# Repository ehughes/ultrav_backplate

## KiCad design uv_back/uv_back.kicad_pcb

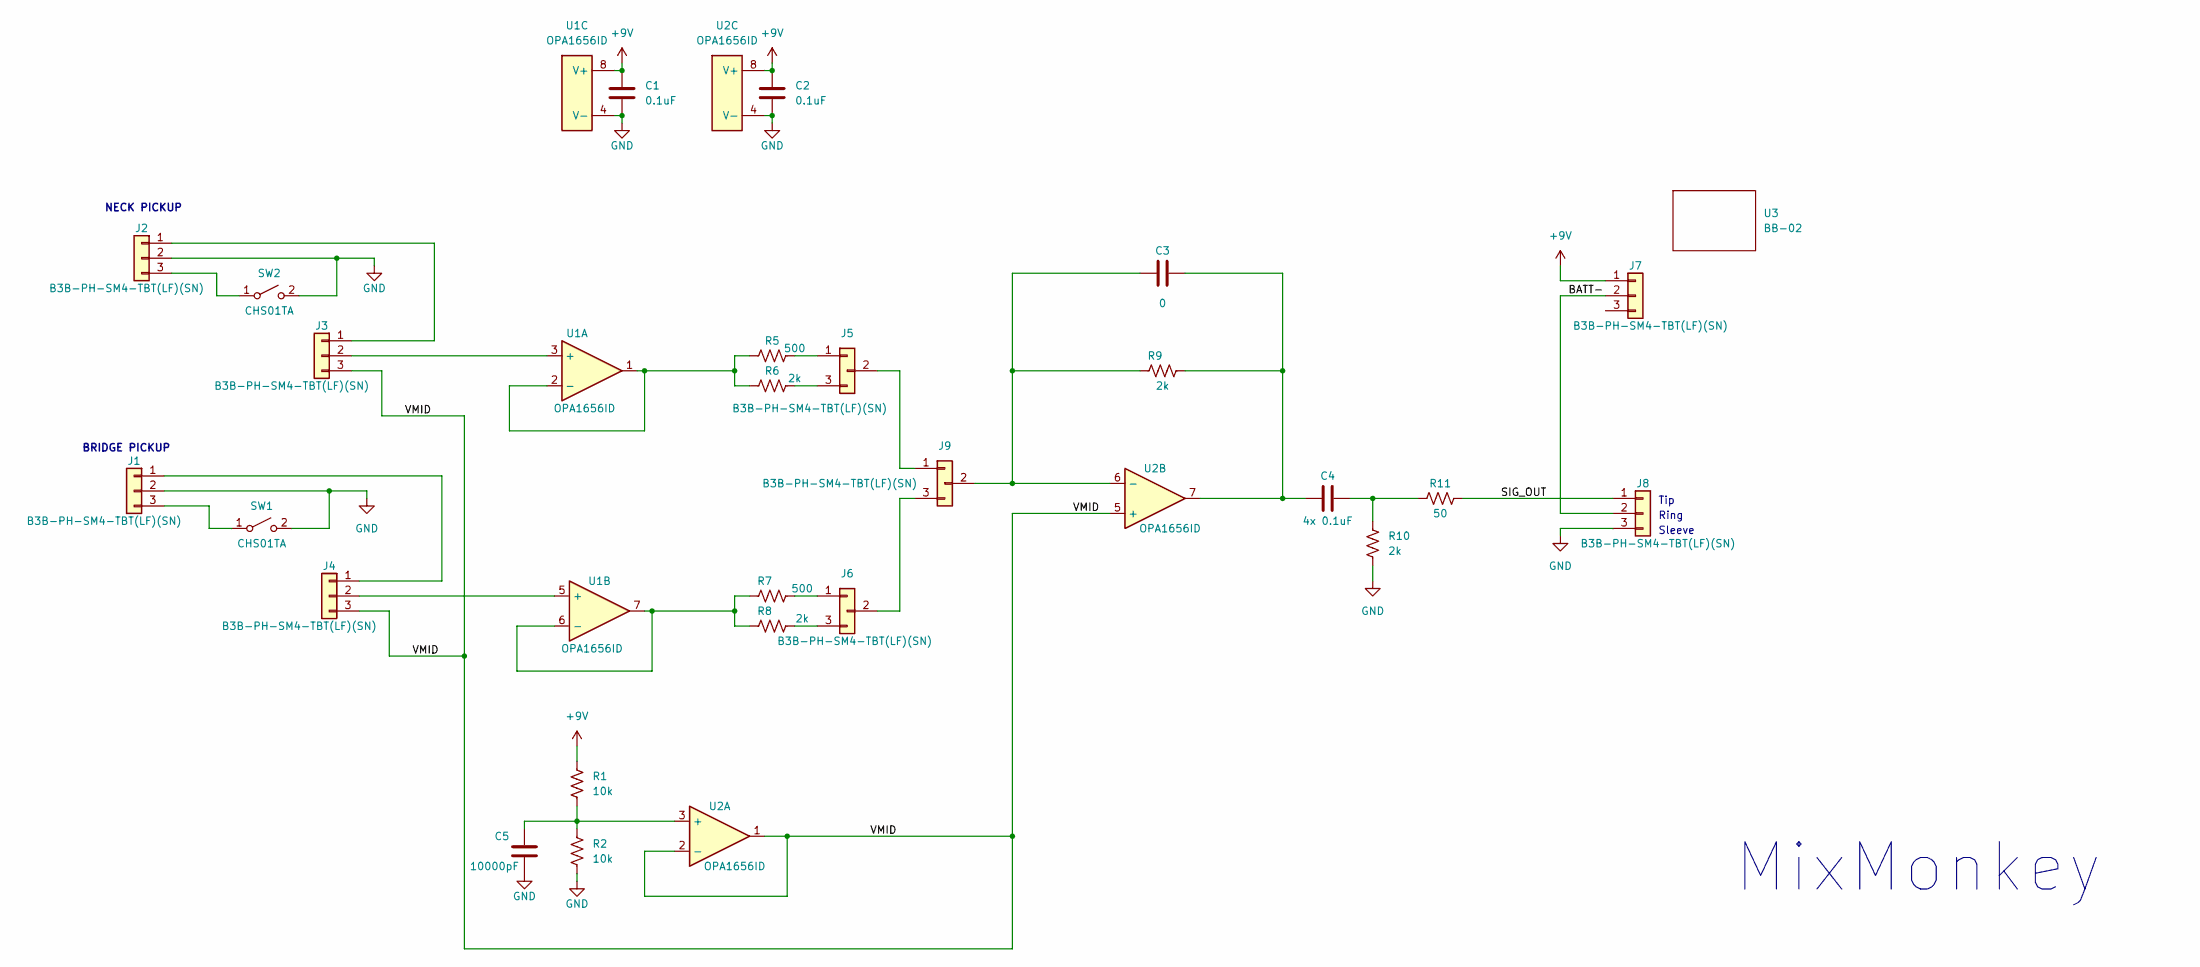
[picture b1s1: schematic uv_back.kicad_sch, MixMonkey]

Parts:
C1, C2: 0.1uF; R_0805_2012Metric_Pad1.20x1.40mm_HandSolder
C3: 0; R_0805_2012Metric_Pad1.20x1.40mm_HandSolder
C4: 4x 0.1uF; C_0805_2012Metric_Pad1.18x1.45mm_HandSolder
C5: 10000pF; R_0805_2012Metric_Pad1.20x1.40mm_HandSolder
J1, J2, J3, J4, J7, J8: B3B-PH-SM4-TBT(LF)(SN); B3B-PH-SM4; MPN B3B-PH-SM4-TBT(LF)(SN)
J5, J6, J9: B3B-PH-SM4-TBT(LF)(SN)_ALT; B3B-PH-SM4; MPN B3B-PH-SM4-TBT(LF)(SN)
R1, R2: 10k; R_0805_2012Metric_Pad1.20x1.40mm_HandSolder
R5, R7: 500; R_0805_2012Metric_Pad1.20x1.40mm_HandSolder
R6, R8, R9, R10: 2k; R_0805_2012Metric_Pad1.20x1.40mm_HandSolder
R11: 50; R_0805_2012Metric_Pad1.20x1.40mm_HandSolder
SW1, SW2: CHS01TA; CHS-01TA; MPN CHS-01TA
U1, U2: OPA1656ID; SOIC-8_3.9x4.9mm_P1.27mm; MPN OPA1656ID
U3: BB-02; BB-04

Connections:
+9V: C1.2, C2.2, J7.1, R1.2, U1.8 (V+), U2.8 (V+)
/BATT-: J7.2, J8.2
/SIG_OUT: J8.1, R11.2
/VMID: J3.3, J4.3, U2.1, U2.2 (-), U2.5 (+)
GND: C1.1, C2.1, C5.1, J1.2, J2.2, J8.3, R2.1, R10.1, SW1.2 (B), SW2.2 (B), U1.4 (V-), U2.4 (V-)
unnamed: C3.1, J9.2, R9.1, U2.6 (-)
unnamed: C3.2, C4.1, R9.2, U2.7
unnamed: C4.2, R10.2, R11.1
unnamed: C5.2, R1.1, R2.2, U2.3 (+)
unnamed: J1.1, J4.1
unnamed: J1.3, SW1.1 (A)
unnamed: J2.1, J3.1
unnamed: J2.3, SW2.1 (A)
unnamed: J3.2, U1.3 (+)
unnamed: J4.2, U1.5 (+)
unnamed: J5.1, R5.2
unnamed: J5.2, J9.1
unnamed: J5.3, R6.2
unnamed: J6.1, R7.2
unnamed: J6.2, J9.3
unnamed: J6.3, R8.2
unnamed: R5.1, R6.1, U1.1, U1.2 (-)
unnamed: R7.1, R8.1, U1.6 (-), U1.7

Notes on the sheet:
Tip
MixMonkey
Ring
BRIDGE PICKUP
NECK PICKUP
Sleeve

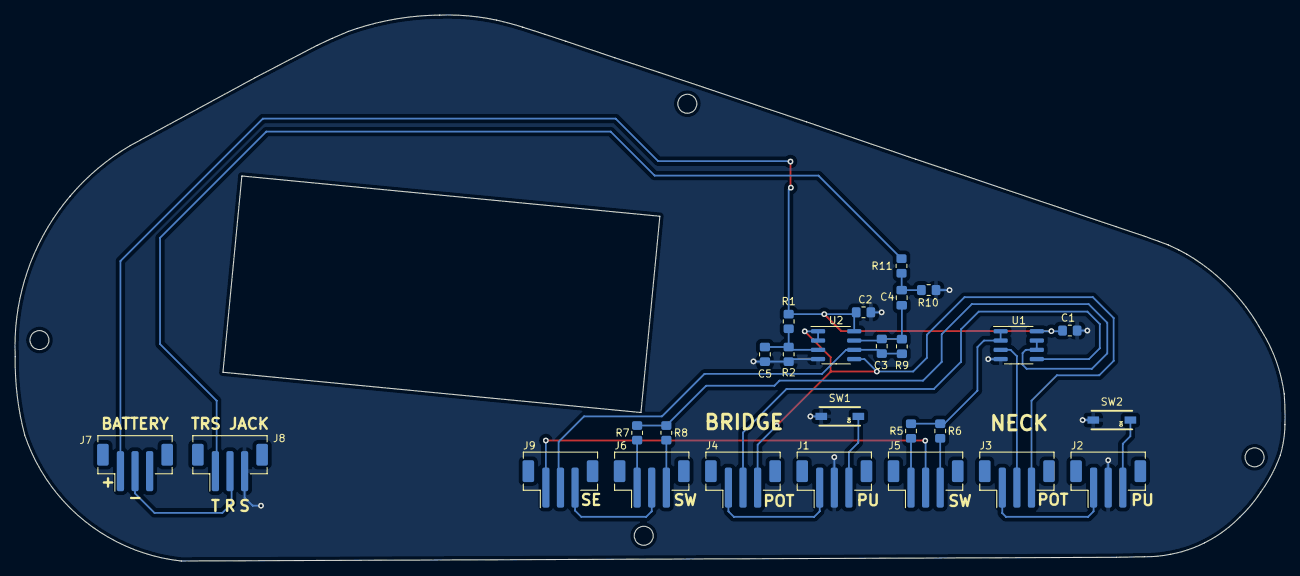
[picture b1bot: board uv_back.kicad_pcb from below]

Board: 2 copper layers, 173.9 x 74.7 mm, 28 parts (27 on the bottom side), 23 nets.

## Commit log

2022-02-06 dev update
2022-02-06 setting up for KiCad v6.01
2022-02-08 roughed out the schematic
2022-02-09 connector and 3d model updates
2022-02-11 1st cut placement
2022-02-11 upated battery holder
2022-02-20 Board Routed. Need to Add Some Bling
2022-02-21 commit before nightly branch
2022-02-21 logos in place
2022-02-22 switched to two layer for outline prototype
2022-03-05 updated as built values
